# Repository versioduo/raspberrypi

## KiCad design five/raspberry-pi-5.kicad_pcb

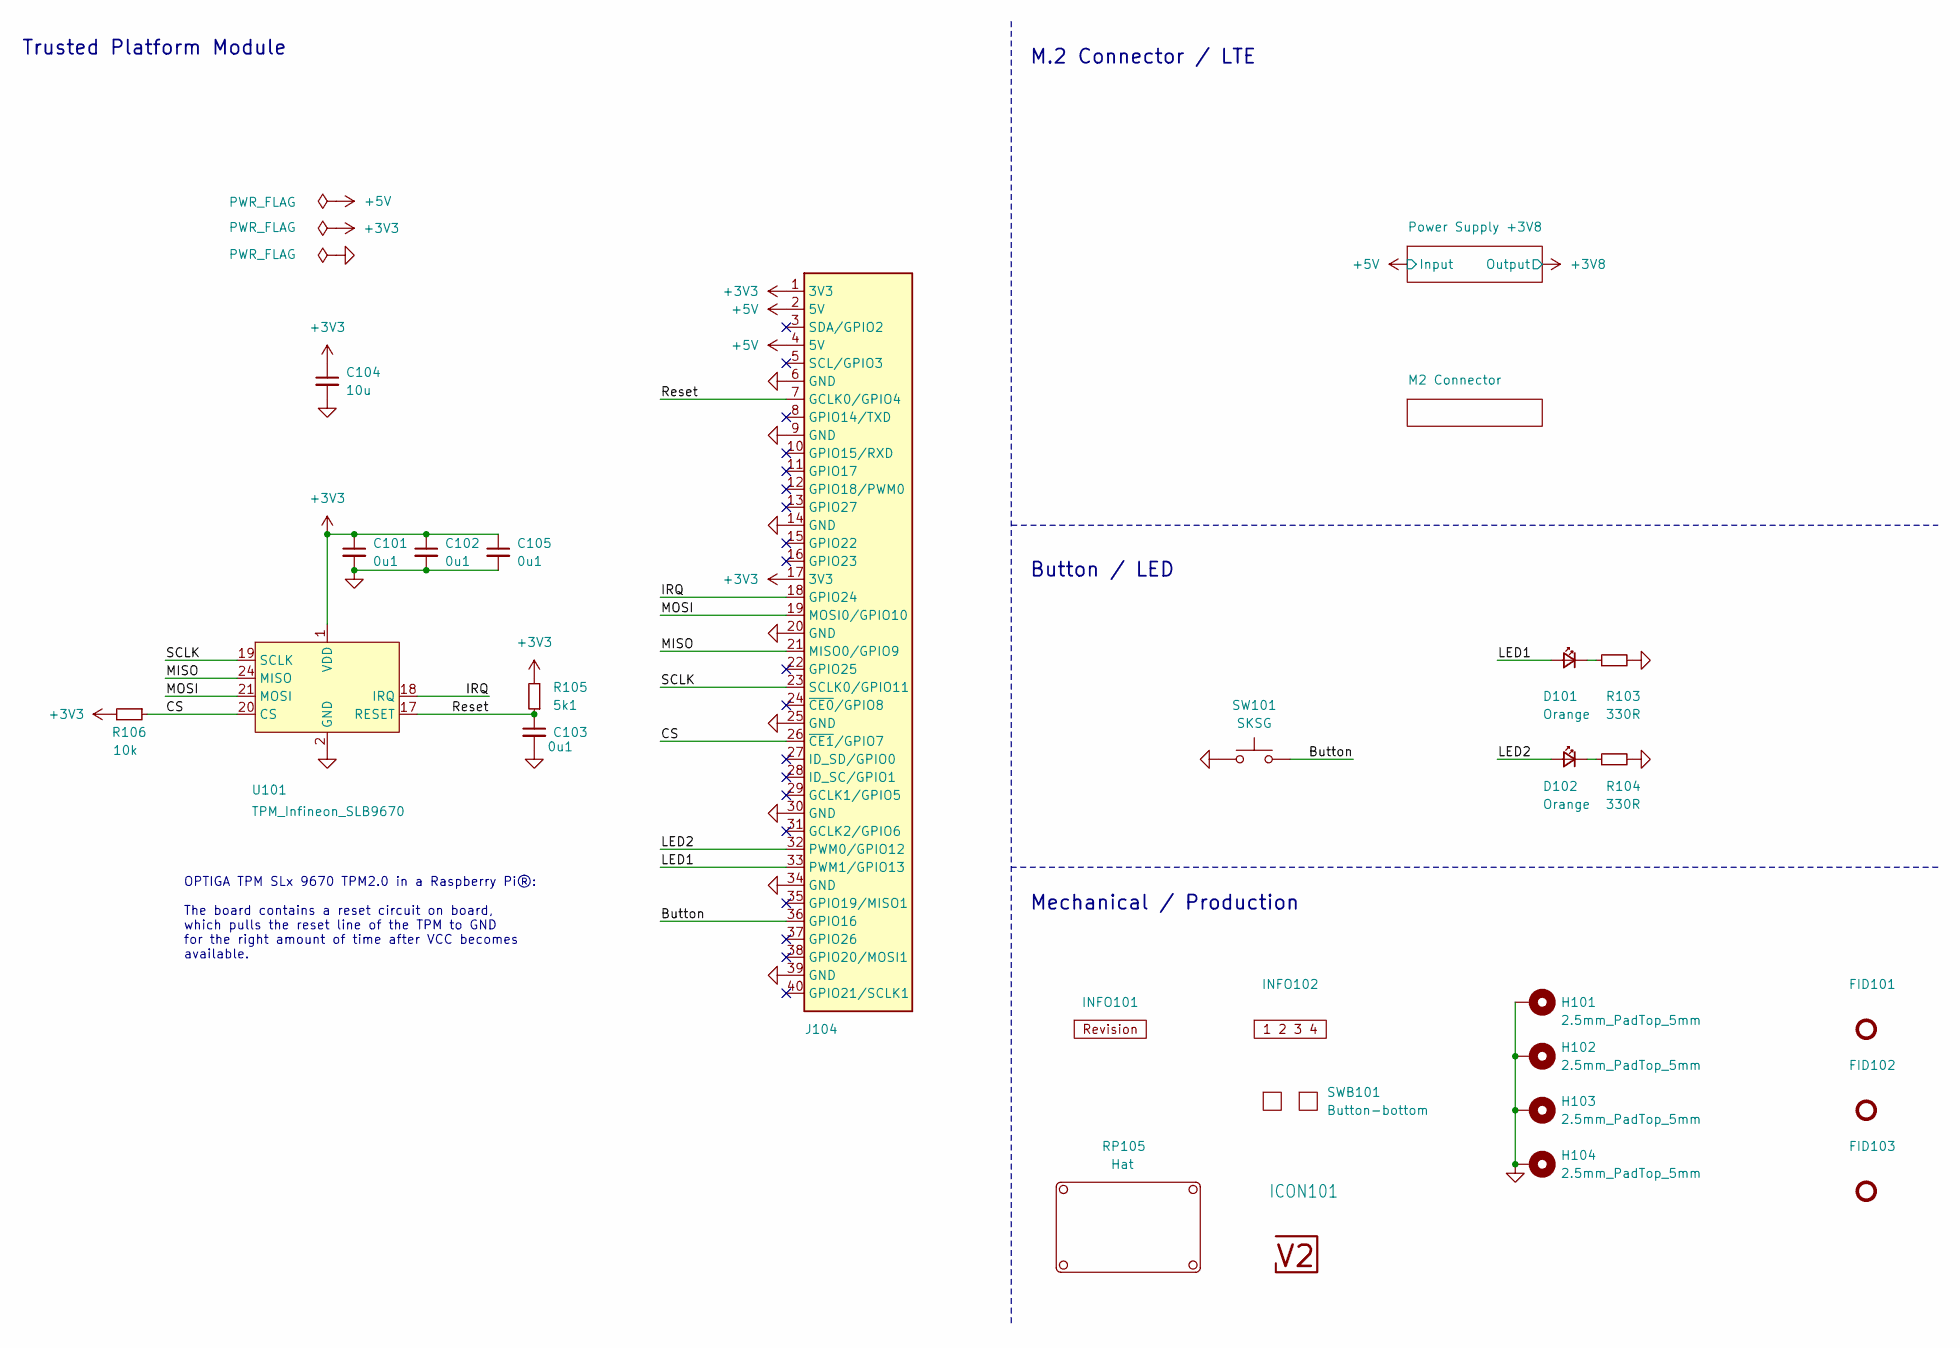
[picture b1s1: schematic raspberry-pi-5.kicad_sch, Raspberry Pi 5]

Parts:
C101, C102, C103, C105: 0u1; C_0603; Rating 50V; Mouser 810-CGA3E2X7R1H104MA
C104: 10u; C_0603; Rating 10V; Mouser 810-C1608X6S1A106M
D101, D102: Orange; LED_0603; Mouser 755-SML-D12D1WT86
FID101, FID102, FID103: Fiducial_Paste; Fiducial_0.5mm_Mask1mm_Paste
H101, H102, H103, H104: 2.5mm_PadTop_5mm; MountingHole_2.5mm_PadTop_5mm
ICON101: V2-logo; Logo_Small
INFO101: Revision
INFO102: Layer_Numbers
J104: Connector
R103, R104: 330R; R_0603; Rating 100mW; Mouser 71-CRCW0603330RFKEAC
R105: 5k1; R_0603; Rating 100mW; Mouser 71-CRCW06035K10FKEAC
R106: 10k; R_0603; Rating 100mW; Mouser 71-CRCW060310K0FKEAC
RP105: Hat
SW101: SKSG; Rating 1.6N; Mouser 688-SKSGACE010
SWB101: Button-bottom; PCB_Button-bottom
U101: TPM_Infineon_SLB9670; QFN-32-1EP_5x5mm_P0.5mm_EP3.6x3.6mm_ThermalVias

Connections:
+3V3: C101.1, C102.1, C104.1, C105.1, J104.1 (3V3), J104.17 (3V3), R105.2, R106.2, U101.1 (VDD), U101.8 (VDD), U101.14 (VDD), U101.22 (VDD)
+5V: J104.2 (5V), J104.4 (5V); also elsewhere on the board
/Button: J104.36 (GPIO16), SW101.2
/CS: J104.26 (~CE1/GPIO7), R106.1, U101.20 (CS)
/IRQ: J104.18 (GPIO24), U101.18 (IRQ)
/LED1: D101.2 (A), J104.33 (PWM1/GPIO13)
/LED2: D102.2 (A), J104.32 (PWM0/GPIO12)
/MISO: J104.21 (MISO0/GPIO9), U101.24 (MISO)
/MOSI: J104.19 (MOSI0/GPIO10), U101.21 (MOSI)
/Reset: C103.1, J104.7 (GCLK0/GPIO4), R105.1, U101.17 (RESET)
/SCLK: J104.23 (SCLK0/GPIO11), U101.19 (SCLK)
GND: C101.2, C102.2, C103.2, C104.2, C105.2, H101.1 (1_1), H102.1 (1_1), H103.1 (1_1), H104.1 (1_1), J104.6 (GND), J104.9 (GND), J104.14 (GND), J104.20 (GND), J104.25 (GND), J104.30 (GND), J104.34 (GND), J104.39 (GND), R103.2, R104.2, SW101.1, U101.2 (GND), U101.9 (GND), U101.16 (GND), U101.23 (GND), U101.32 (GND), U101.33 (GND); also elsewhere on the board
unnamed: D101.1 (K), R103.1
unnamed: D102.1 (K), R104.1

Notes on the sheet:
Button / LED
Trusted Platform Module
Mechanical / Production
OPTIGA TPM SLx 9670 TPM2.0 in a Raspberry Pi®: The board contains a reset circuit on board, which pulls the reset line of the TPM to GND for the right amount of time after VCC becomes available.
M.2 Connector / LTE

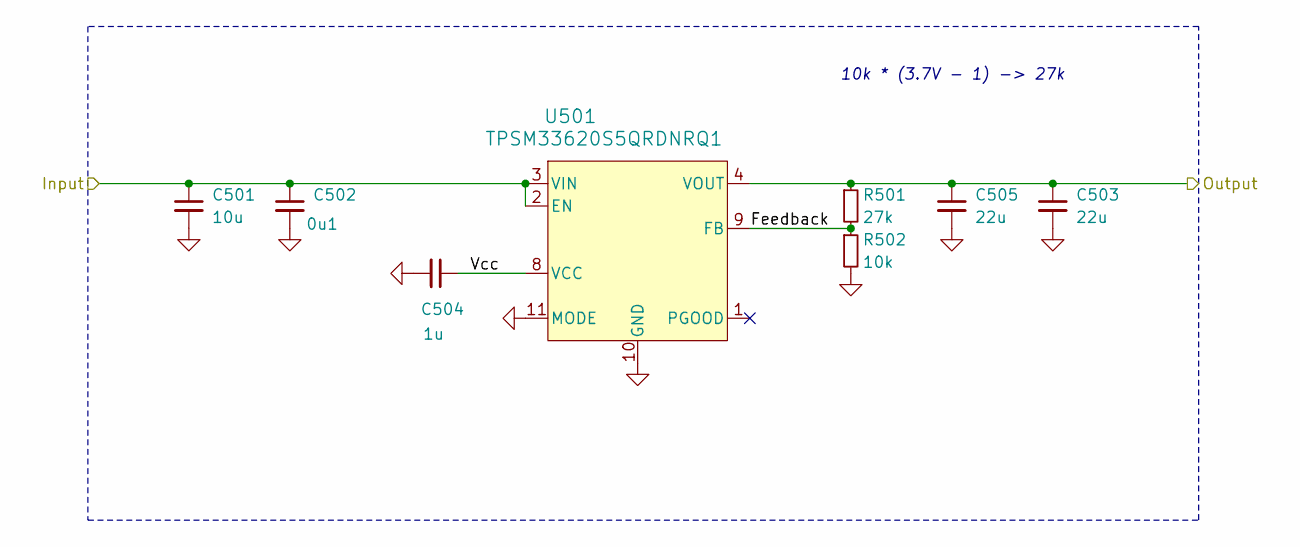
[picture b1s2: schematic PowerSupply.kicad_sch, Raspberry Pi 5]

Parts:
C501: 10u; C_1210; Rating 50V; Mouser 810-CNC6P1X7R1H106K2
C502: 0u1; C_0603; Rating 50V; Mouser 810-CGA3E2X7R1H104MA
C503, C505: 22u; C_1210; Rating 25V; Mouser 810-CGA6P3X7R1E226M5
C504: 1u; C_0603; Rating 50V; Mouser 810-CGA3E3X7R1H105K0
R501: 27k; R_0603
R502: 10k; R_0603; Rating 100mW; Mouser 71-CRCW060310K0FKEAC
U501: TPSM33620S5QRDNRQ1; QFN-11; Rating 2A; Mouser 595-SM33620S5QRDNRQ1

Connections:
+3V8: C503.1, C505.1, R501.1, U501.4 (VOUT); also elsewhere on the board
+5V: C501.1, C502.1, U501.2 (EN), U501.3 (VIN); also elsewhere on the board
/Power Supply +3V8/Feedback: R501.2, R502.1, U501.9 (FB)
/Power Supply +3V8/Vcc: C504.1, U501.8 (VCC)
GND: C501.2, C502.2, C503.2, C504.2, C505.2, R502.2, U501.10 (GND), U501.11 (MODE); also elsewhere on the board

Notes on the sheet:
10k * (3.7V - 1) -> 27k

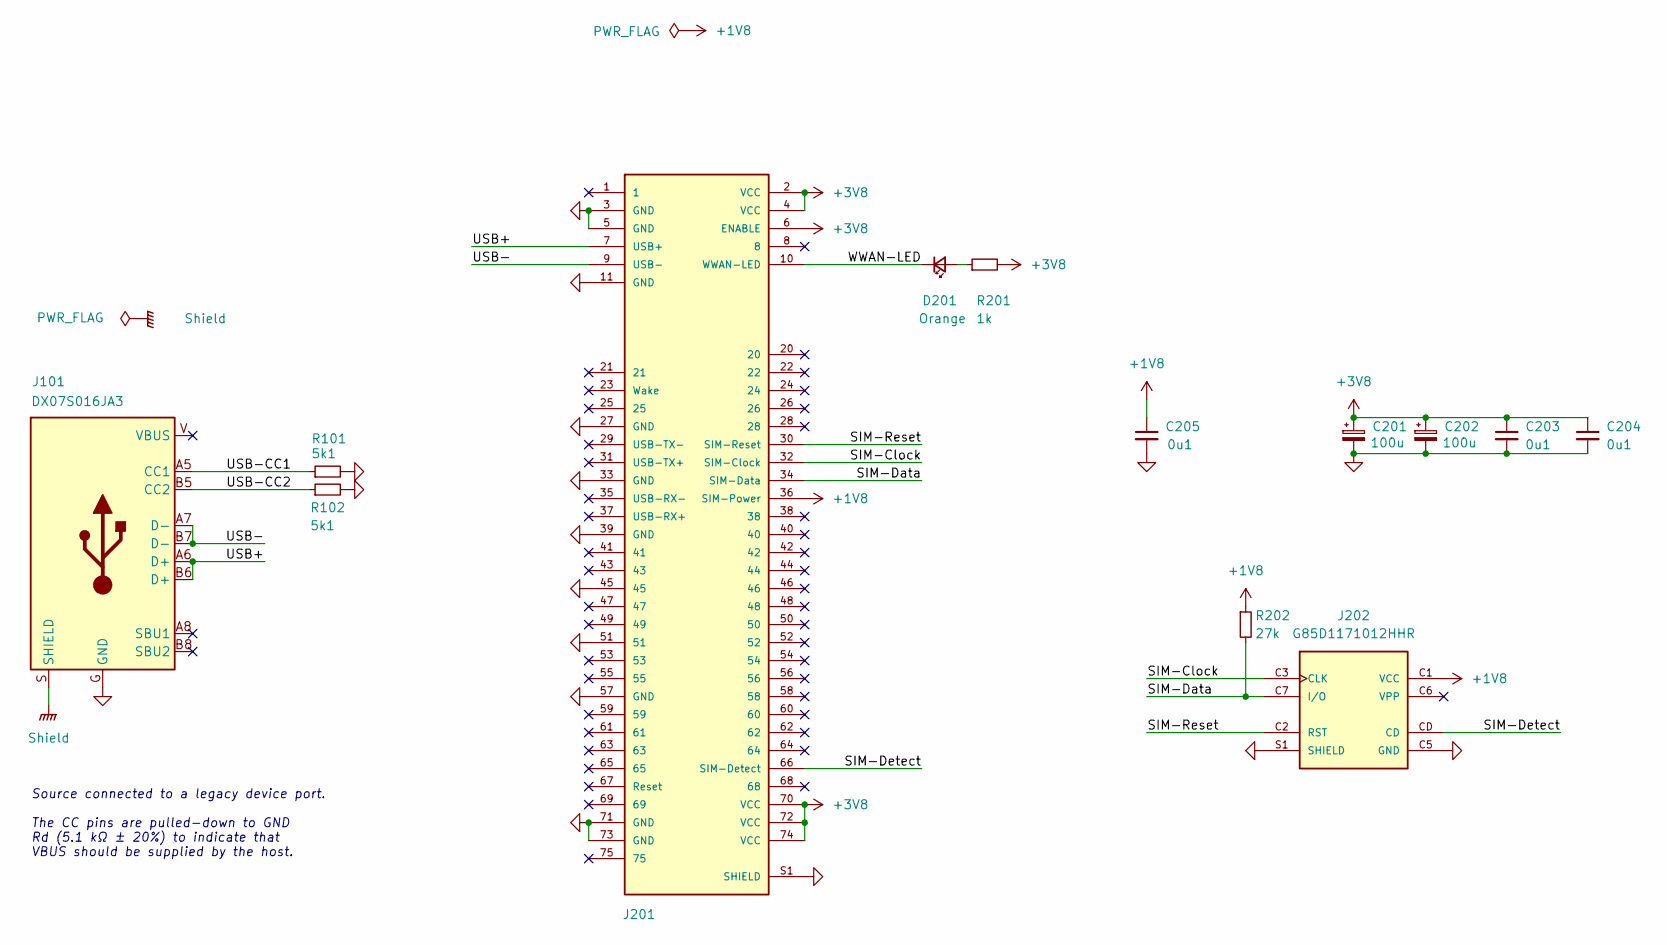
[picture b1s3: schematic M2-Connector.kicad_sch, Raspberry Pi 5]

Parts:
C201, C202: 100u; EIA3528; Mouser 80-T491B107K006
C203, C204, C205: 0u1; C_0603; Rating 50V; Mouser 810-CGA3E2X7R1H104MA
D201: Orange; LED_0603; Mouser 755-SML-D12D1WT86
J101: DX07S016JA3; JAE_DX07S016JA3; Mouser 656-DX07S016JA3R1500
J201: MDT180B01001
J202: G85D1171012HHR; Amphenol_G85D1171012HHR
R101, R102: 5k1; R_0603; Rating 100mW; Mouser 71-CRCW06035K10FKEAC
R201: 1k; R_0603; Rating 330mW; Mouser 71-CRCW06031K00FKEAH
R202: 27k; R_0603

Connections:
+1V8: C205.1, J201.36 (SIM-Power), J202.C1 (VCC), R202.1
+3V8: C201.1, C202.1, C203.1, C204.1, J201.2 (VCC), J201.4 (VCC), J201.6 (ENABLE), J201.70 (VCC), J201.72 (VCC), J201.74 (VCC), R201.2; also elsewhere on the board
/M2 Connector/SIM-Clock: J201.32 (SIM-Clock), J202.C3 (CLK)
/M2 Connector/SIM-Data: J201.34 (SIM-Data), J202.C7 (I/O), R202.2
/M2 Connector/SIM-Detect: J201.66 (SIM-Detect), J202.CD
/M2 Connector/SIM-Reset: J201.30 (SIM-Reset), J202.C2 (RST)
/M2 Connector/Shield: J101.S (SHIELD)
/M2 Connector/USB+: J101.A6 (D+), J101.B6 (D+), J201.7 (USB+)
/M2 Connector/USB-: J101.A7 (D-), J101.B7 (D-), J201.9 (USB-)
/M2 Connector/USB-CC1: J101.A5 (CC1), R101.1
/M2 Connector/USB-CC2: J101.B5 (CC2), R102.1
/M2 Connector/WWAN-LED: D201.1 (K), J201.10 (WWAN-LED)
GND: C201.2, C202.2, C203.2, C204.2, C205.2, J101.G (GND), J201.3 (GND), J201.5 (GND), J201.11 (GND), J201.27 (GND), J201.33 (GND), J201.39 (GND), J201.45, J201.51, J201.57 (GND), J201.71 (GND), J201.73 (GND), J201.S1 (SHIELD), J201.S2 (SHIELD), J201.SCREW (SHIELD), J202.C5 (GND), J202.S1 (SHIELD), J202.S2 (SHIELD), J202.S3 (SHIELD), J202.S4 (SHIELD), R101.2, R102.2; also elsewhere on the board
unnamed: D201.2 (A), R201.1

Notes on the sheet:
﻿Source connected to a legacy device port. The CC pins are pulled-down to GND Rd (5.1 kΩ ± 20%) to indicate that VBUS should be supplied by the host.

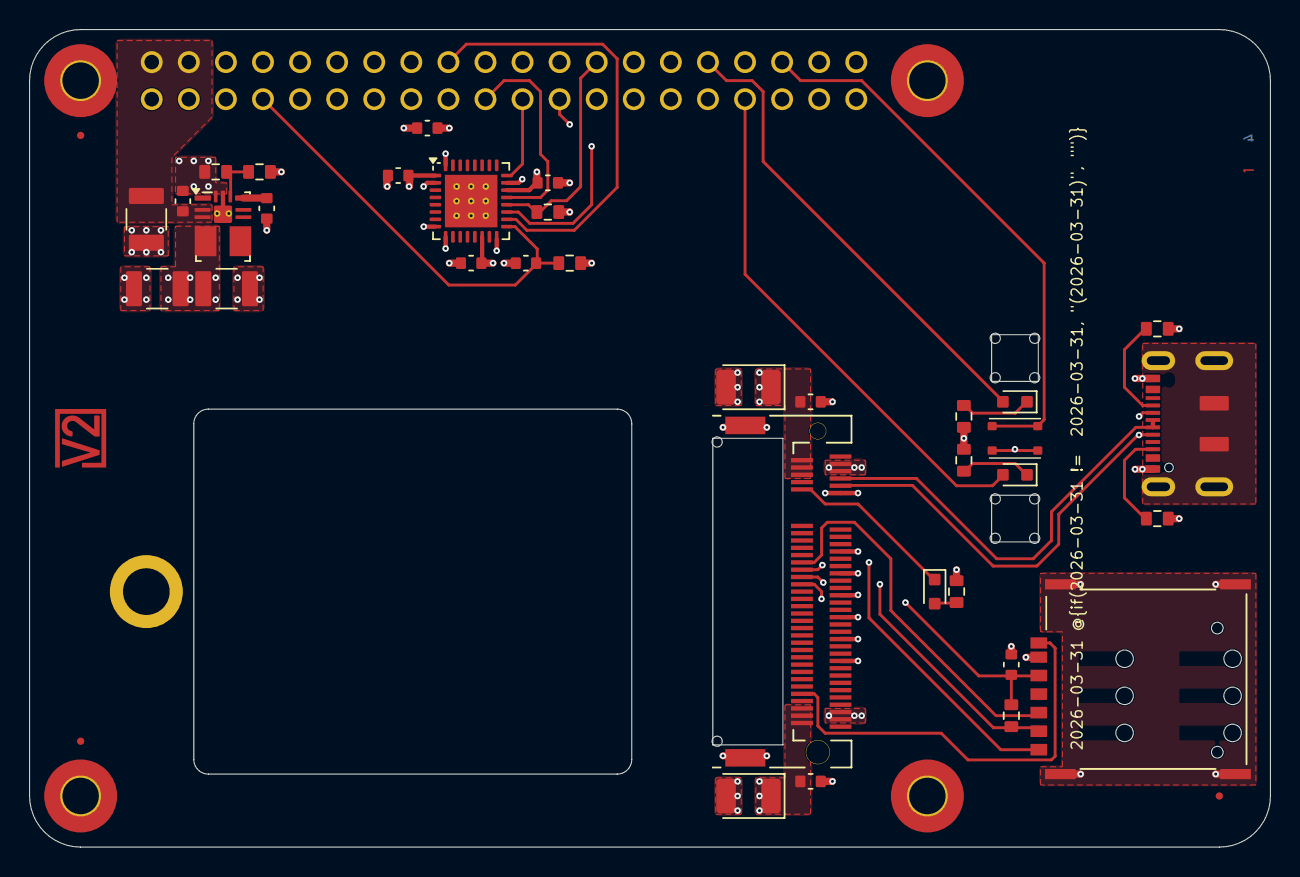
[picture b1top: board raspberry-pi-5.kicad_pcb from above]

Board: 4 copper layers, 85.0 x 56.0 mm, 47 parts (0 on the bottom side), 28 nets.

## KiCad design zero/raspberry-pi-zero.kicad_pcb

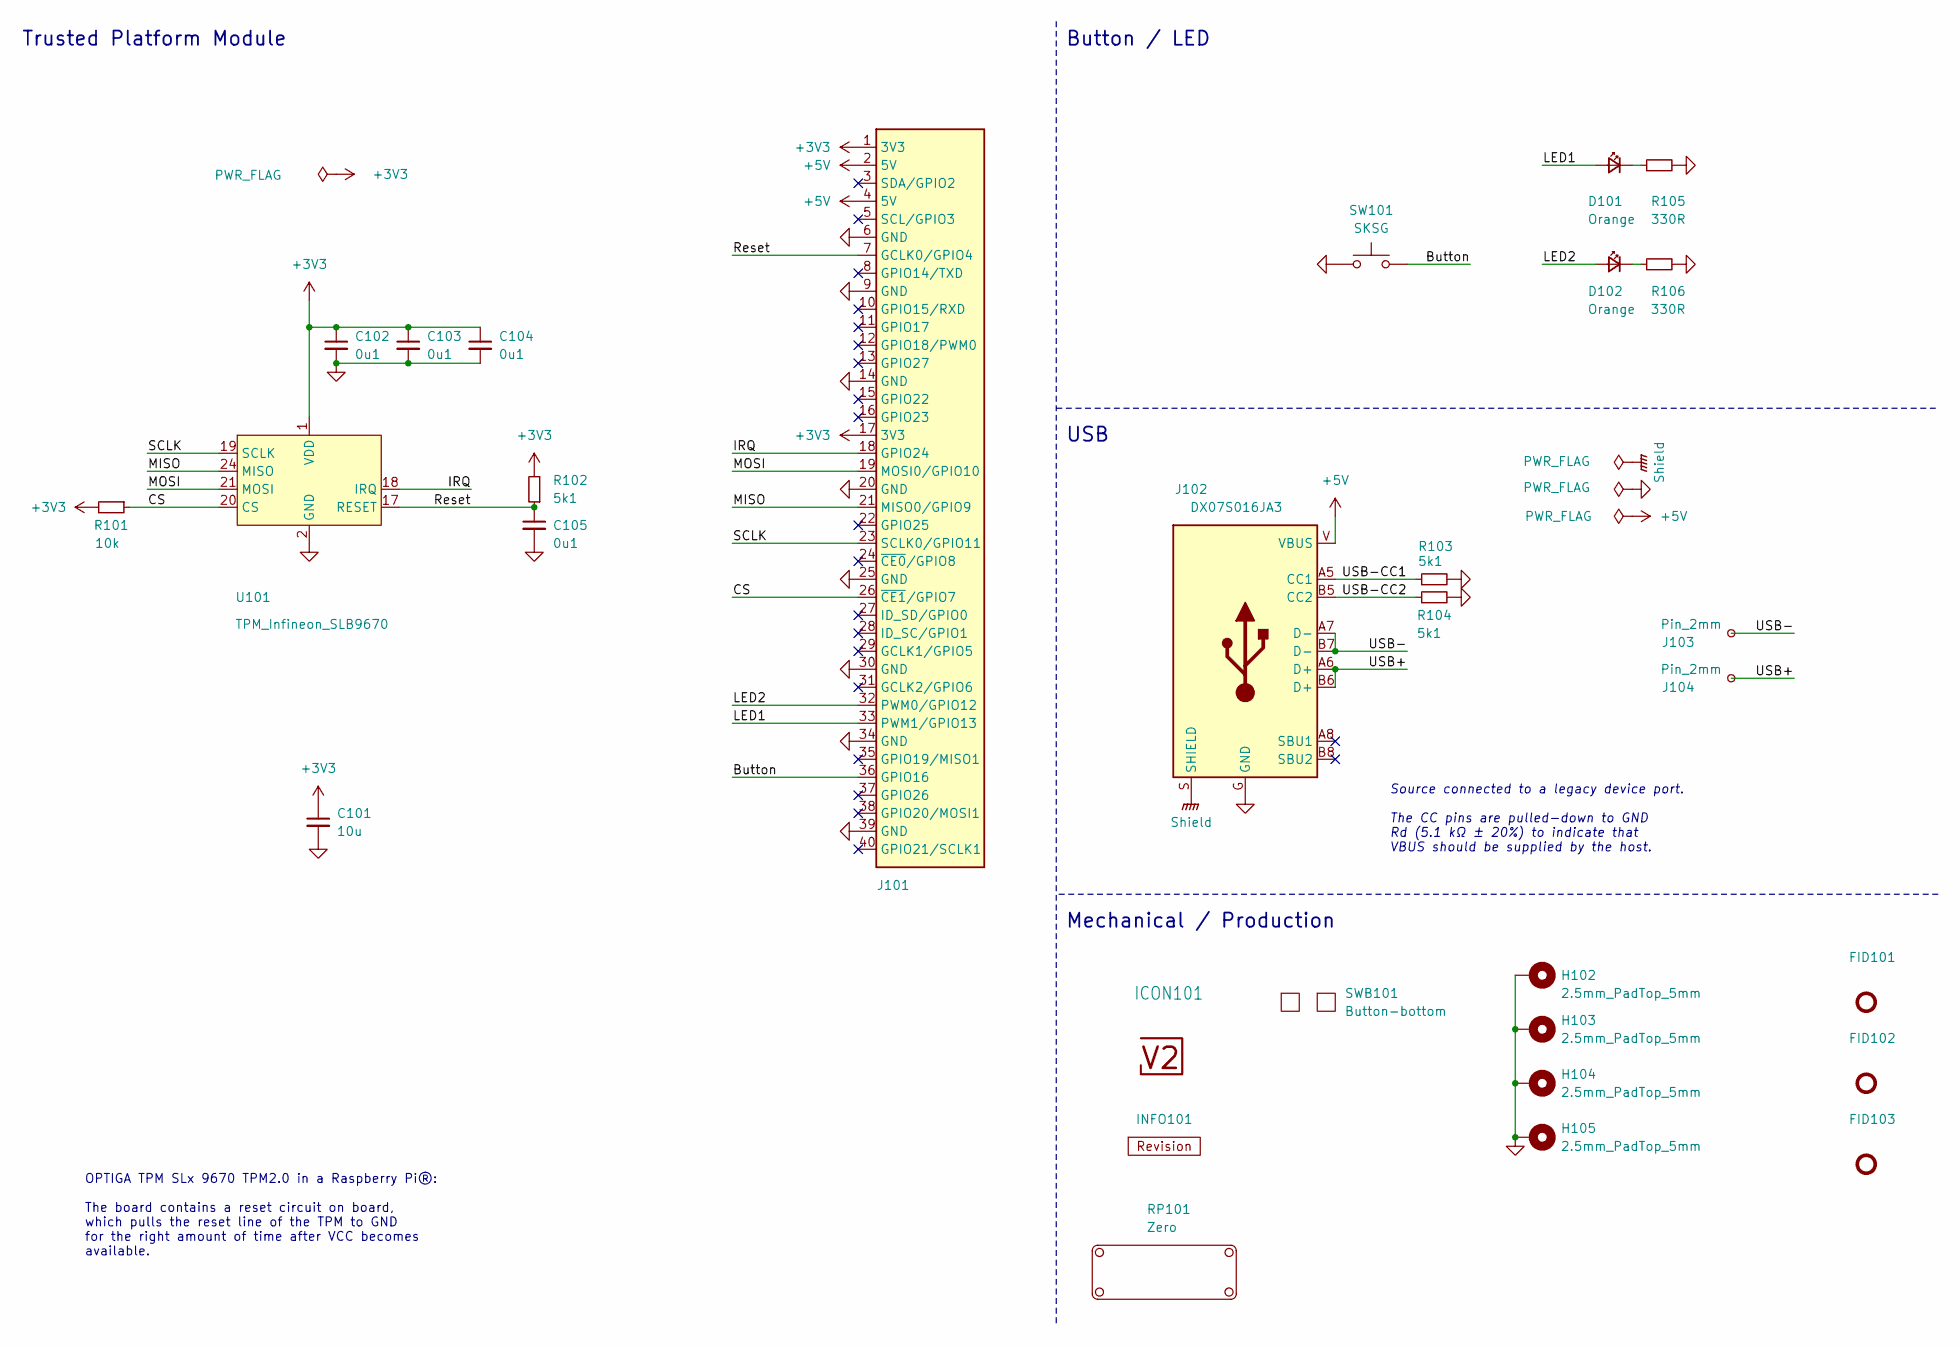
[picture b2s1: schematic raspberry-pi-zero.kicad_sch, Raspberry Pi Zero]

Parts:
C101: 10u; C_0603; Rating 10V; Mouser 810-C1608X6S1A106M
C102, C103, C104, C105: 0u1; C_0603; Rating 50V; Mouser 810-CGA3E2X7R1H104MA
D101, D102: Orange; LED_0603; Mouser 755-SML-D12D1WT86
FID101, FID102, FID103: Fiducial_Paste; Fiducial_0.5mm_Mask1mm_Paste
H102, H103, H104, H105: 2.5mm_PadTop_5mm; MountingHole_2.5mm_PadTop_5mm
ICON101: V2-logo; Logo_Small
INFO101: Revision
J101: Connector_PogoPins
J102: DX07S016JA3; JAE_DX07S016JA3; Mouser 656-DX07S016JA3R1500
J103, J104: Pin_2mm
R101: 10k; R_0603; Rating 100mW; Mouser 71-CRCW060310K0FKEAC
R102, R103, R104: 5k1; R_0603; Rating 100mW; Mouser 71-CRCW06035K10FKEAC
R105, R106: 330R; R_0603; Rating 100mW; Mouser 71-CRCW0603330RFKEAC
RP101: Zero
SW101: SKSG; Mouser 688-SKSGACE010
SWB101: Button-bottom; PCB_Button-bottom
U101: TPM_Infineon_SLB9670; QFN-32-1EP_5x5mm_P0.5mm_EP3.6x3.6mm_ThermalVias

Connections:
+3V3: C101.1, C102.1, C103.1, C104.1, J101.1 (3V3), J101.17 (3V3), R101.2, R102.2, U101.1 (VDD), U101.8 (VDD), U101.14 (VDD), U101.22 (VDD)
+5V: J101.2 (5V), J101.4 (5V), J102.V (VBUS)
/Button: J101.36 (GPIO16), SW101.2
/CS: J101.26 (~CE1/GPIO7), R101.1, U101.20 (CS)
/IRQ: J101.18 (GPIO24), U101.18 (IRQ)
/LED1: D101.2 (A), J101.33 (PWM1/GPIO13)
/LED2: D102.2 (A), J101.32 (PWM0/GPIO12)
/MISO: J101.21 (MISO0/GPIO9), U101.24 (MISO)
/MOSI: J101.19 (MOSI0/GPIO10), U101.21 (MOSI)
/Reset: C105.1, J101.7 (GCLK0/GPIO4), R102.1, U101.17 (RESET)
/SCLK: J101.23 (SCLK0/GPIO11), U101.19 (SCLK)
/USB+: J102.A6 (D+), J102.B6 (D+), J104.1
/USB-: J102.A7 (D-), J102.B7 (D-), J103.1
/USB-CC1: J102.A5 (CC1), R103.1
/USB-CC2: J102.B5 (CC2), R104.1
GND: C101.2, C102.2, C103.2, C104.2, C105.2, H102.1, H103.1, H104.1, H105.1, J101.6 (GND), J101.9 (GND), J101.14 (GND), J101.20 (GND), J101.25 (GND), J101.30 (GND), J101.34 (GND), J101.39 (GND), J102.G (GND), R103.2, R104.2, R105.2, R106.2, SW101.1, U101.2 (GND), U101.9 (GND), U101.16 (GND), U101.23 (GND), U101.32 (GND), U101.33 (GND)
unnamed: D101.1 (K), R105.1
unnamed: D102.1 (K), R106.1
Shield: J102.S (SHIELD)

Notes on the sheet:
Button / LED
Trusted Platform Module
﻿Source connected to a legacy device port. The CC pins are pulled-down to GND Rd (5.1 kΩ ± 20%) to indicate that VBUS should be supplied by the host.
Mechanical / Production
OPTIGA TPM SLx 9670 TPM2.0 in a Raspberry Pi®: The board contains a reset circuit on board, which pulls the reset line of the TPM to GND for the right amount of time after VCC becomes available.
USB

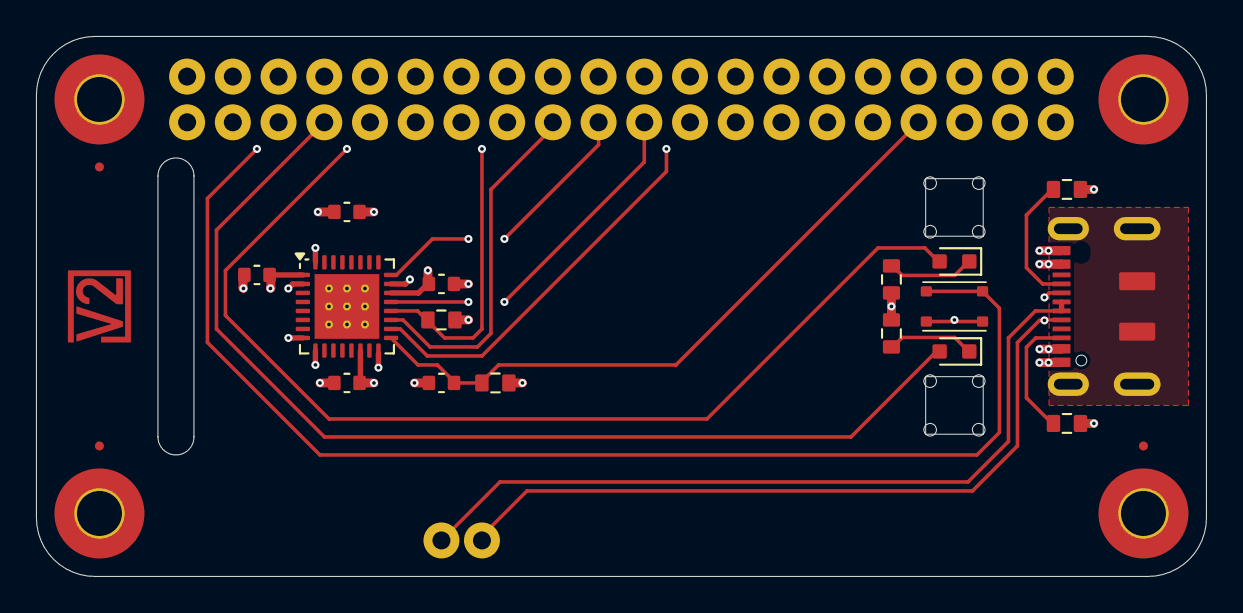
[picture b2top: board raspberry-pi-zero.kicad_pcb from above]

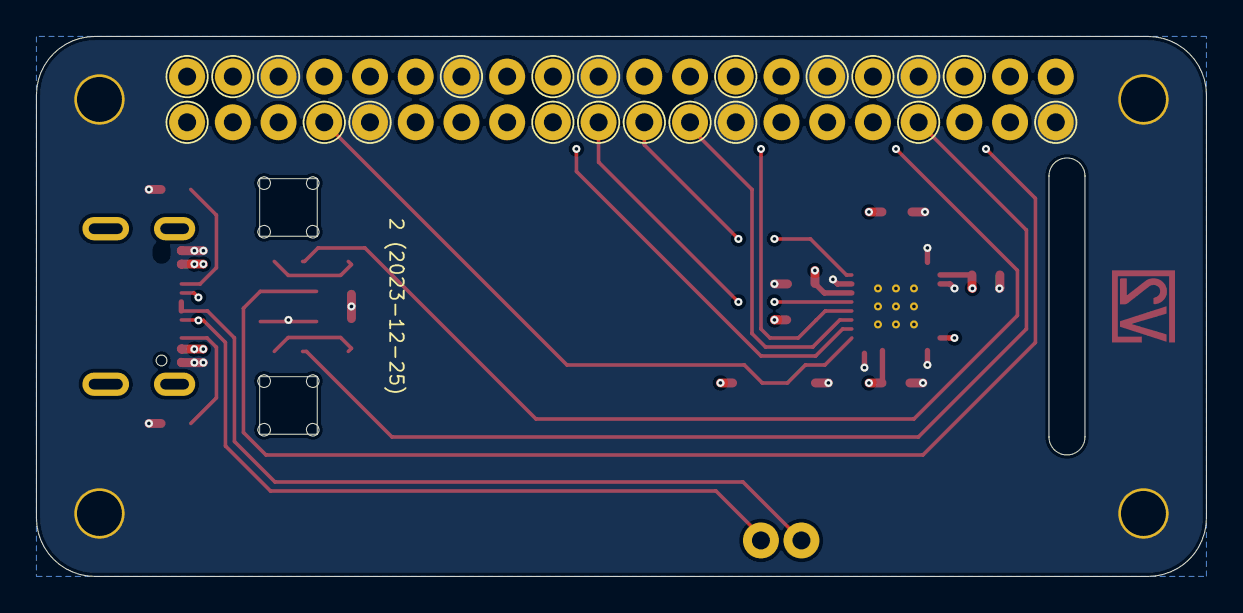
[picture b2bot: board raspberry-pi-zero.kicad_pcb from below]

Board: 4 copper layers, 65.0 x 30.0 mm, 30 parts (2 on the bottom side), 18 nets.

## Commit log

2025-12-28 Import
2026-02-15 Update Library
2026-03-26 KiCad 10
2026-03-26 Refresh
2026-03-31 Replace step-down
2026-05-11 Good Bye Imperial
